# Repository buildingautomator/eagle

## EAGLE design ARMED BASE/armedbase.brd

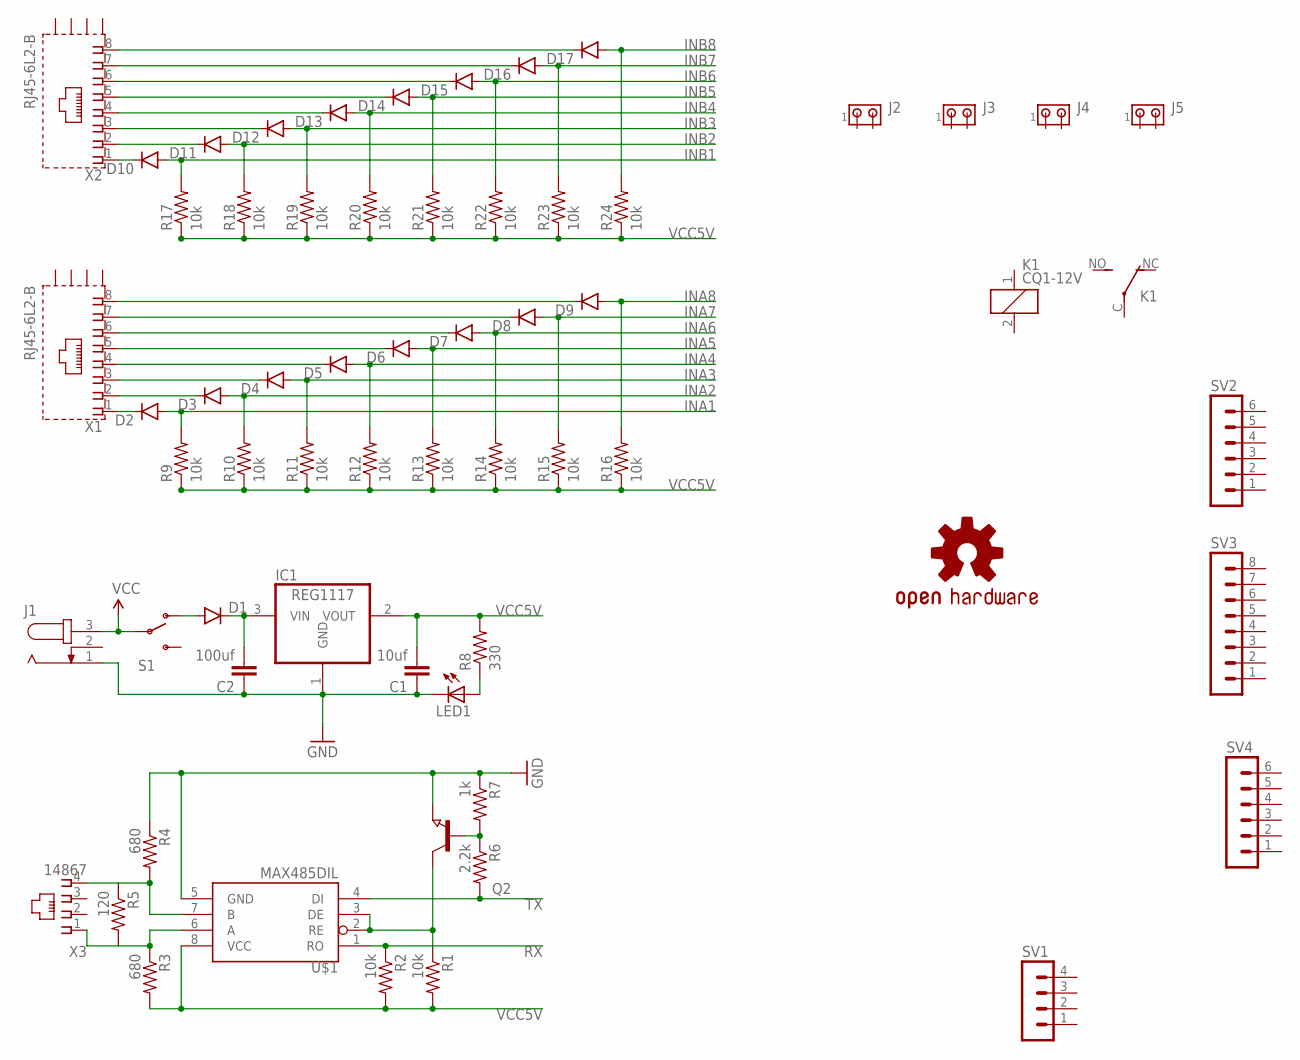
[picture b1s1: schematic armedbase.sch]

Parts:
C1: 10uf; 0805
C2: 100uf; 0805
D1, D2, D3, D4, D5, D6, D7, D8, D9, D10, D11, D12, D13, D14, D15, D16, D17: DIODESMA; SMA-DIODE
IC1: REG1117; SOT223
J1: JACK-PLUG1; SPC4078
J2, J3, J4, J5: MTA02-156; 1X2MTA
K1: CQ1-12V; CQ1
LED1: LEDCHIP-LED0805; CHIP-LED0805
LOGO2: OSHW-LOGOL; OSHW-LOGO-L
Q2: NPN-TRANSISTOR_SOT23; SOT23
R1, R2, R9, R10, R11, R12, R13, R14, R15, R16, R17, R18, R19, R20, R21, R22, R23, R24: 10k; 0805
R3, R4: 680; 0805
R5: 120; 0805
R6: 2.2k; 0805
R7: 1k; 0805
R8: 330; 0805
S1: SWITCH-SPDTSMD2; SWITCH-SPDT-SMD
SV1: MA04-1
SV2, SV4: MA06-1
SV3: MA08-1
U$1: MAX485DIL; DIL08
X1, X2: RJ45-6L2-B; RJ45-SHIELD2
X3: 14867

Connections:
GND: C1.1, C2.1, IC1.1 (GND), J1.1, LED1.C, Q2.2 (E), R4.1, R7.1, U$1.5 (GND)
INA1: D2.A, R9.2
INA2: D3.A, R10.2
INA3: D4.A, R11.2
INA4: D5.A, R12.2
INA5: D6.A, R13.2
INA6: D7.A, R14.2
INA7: D8.A, R15.2
INA8: D9.A, R16.2
INB1: D10.A, R17.2
INB2: D11.A, R18.2
INB3: D12.A, R19.2
INB4: D13.A, R20.2
INB5: D14.A, R21.2
INB6: D15.A, R22.2
INB7: D16.A, R23.2
INB8: D17.A, R24.2
unnamed: D2.C, X1.1
unnamed: Q2.3 (C), R1.1, U$1.2 (RE), U$1.3 (DE)
unnamed: D10.C, X2.1
unnamed: Q2.1 (B), R6.1, R7.2
unnamed: D11.C, X2.2
unnamed: R4.2, R5.1, U$1.7 (B), X3.4
unnamed: R3.1, R5.2, U$1.6 (A), X3.1
unnamed: D12.C, X2.3
unnamed: D13.C, X2.4
unnamed: LED1.A, R8.1
unnamed: D14.C, X2.5
unnamed: D1.A, S1.1 (O)
unnamed: C2.2, D1.C, IC1.3 (VIN)
unnamed: D15.C, X2.6
unnamed: D16.C, X2.7
unnamed: D17.C, X2.8
unnamed: D3.C, X1.2
unnamed: D4.C, X1.3
unnamed: D5.C, X1.4
unnamed: D6.C, X1.5
unnamed: D7.C, X1.6
unnamed: D8.C, X1.7
unnamed: D9.C, X1.8
RX: R2.1, U$1.1 (RO)
TX: R6.2, U$1.4 (DI)
VCC: J1.3, S1.2
VCC5V: C1.2, IC1.2 (VOUT), R1.2, R2.2, R3.2, R8.2, R9.1, R10.1, R11.1, R12.1, R13.1, R14.1, R15.1, R16.1, R17.1, R18.1, R19.1, R20.1, R21.1, R22.1, R23.1, R24.1, U$1.8 (VCC)

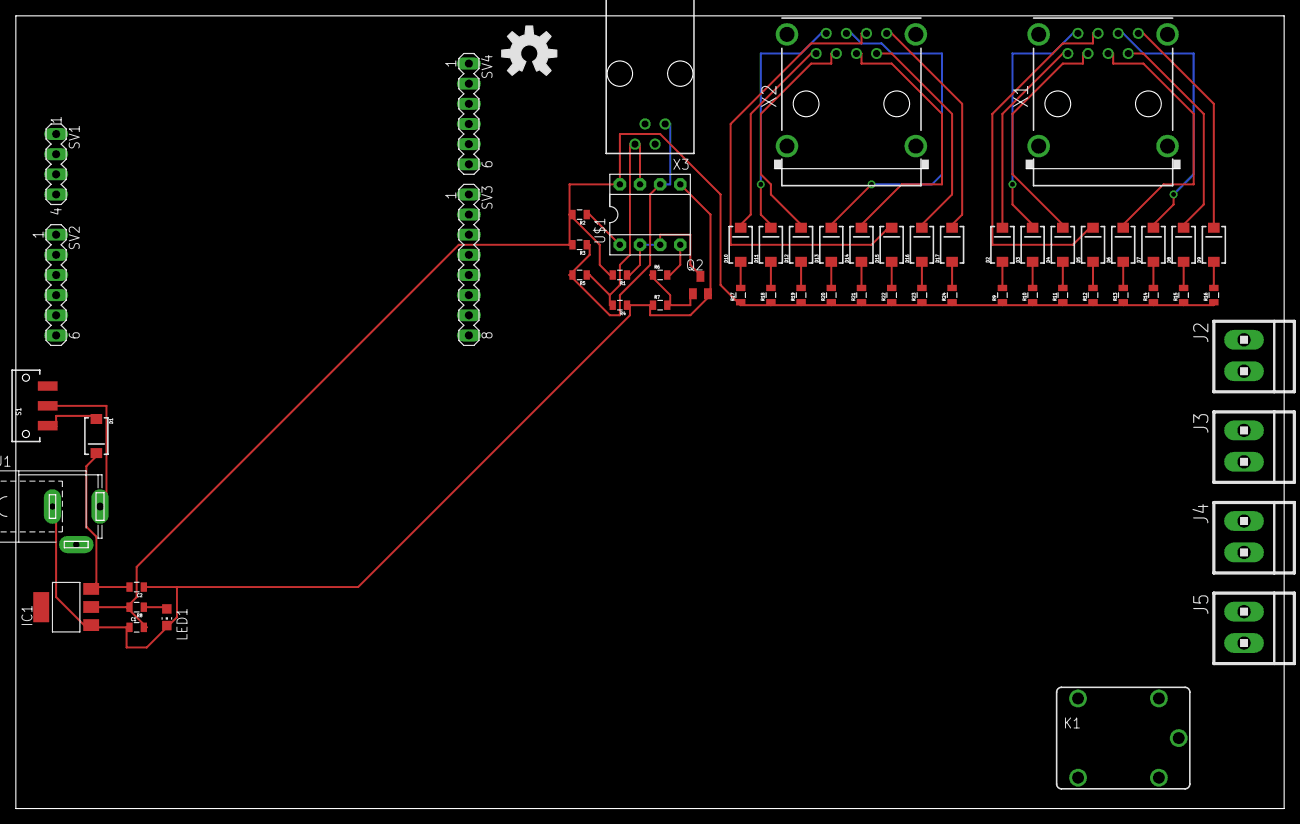
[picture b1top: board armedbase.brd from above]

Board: 2 copper layers, 160.0 x 100.0 mm, 62 parts (0 on the bottom side), 44 nets.

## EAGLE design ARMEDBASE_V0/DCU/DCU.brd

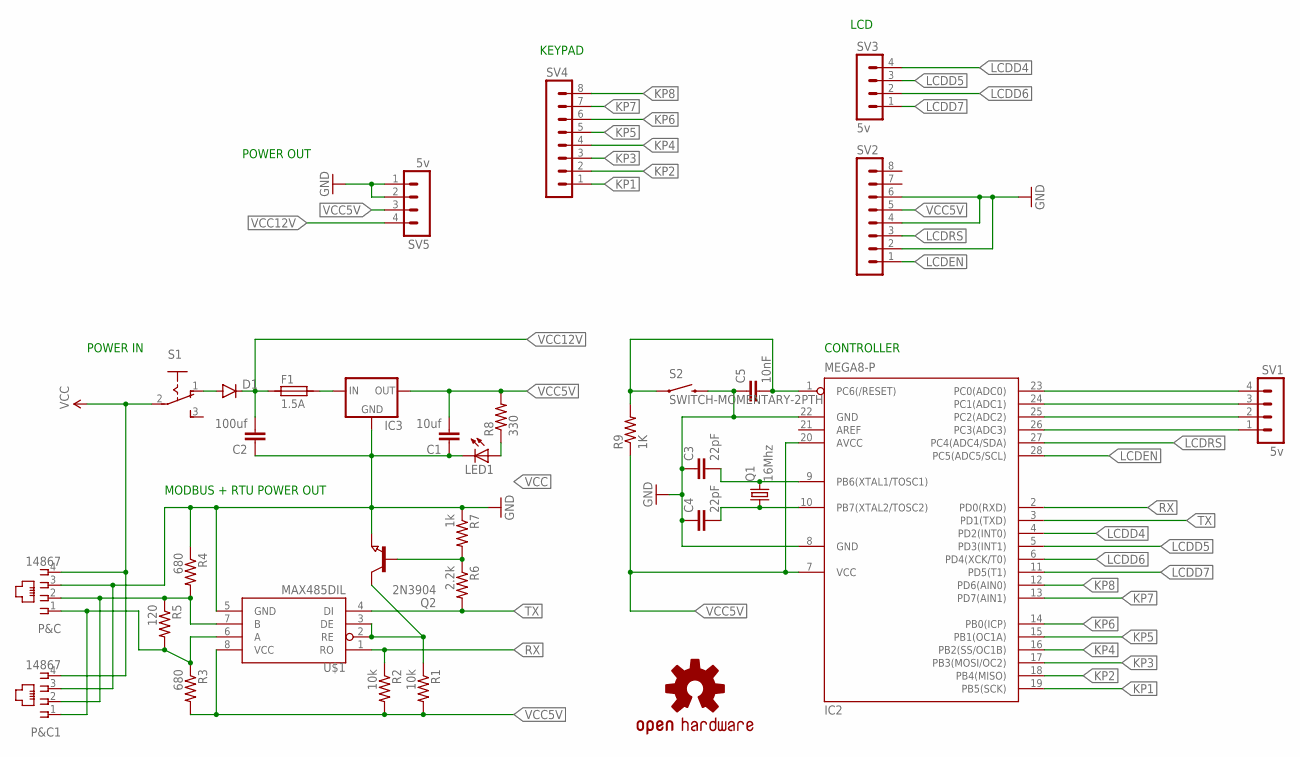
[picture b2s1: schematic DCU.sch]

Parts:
C1: 10uf; 0805
C2: 100uf; 0805
C3, C4: 22pF; 0805
C5: 10nF; 0805
D1: DIODESMA; SMA-DIODE
F1: 1.5A; 1820
IC2: MEGA8-P; DIL28-3
IC3: V_REG_78XX-TO-220; TO-220-ALT
LED1: LEDCHIP-LED0805; CHIP-LED0805
LOGO1: OSHW-LOGOL; OSHW-LOGO-L
P&C, P&C1: 14867
Q1: 16Mhz; SM49
Q2: 2N3904; SOT23
R1, R2: 10k; 0805
R3, R4: 680; 0805
R5: 120; 0805
R6: 2.2k; 0805
R7: 1k; 0805
R8: 330; 0805
R9: 1K; 0805
S1: 255SB
S2: SWITCH-MOMENTARY-2PTH; TACTILE-PTH
SV1, SV3, SV5: 5v; MA04-1
SV2, SV4: MA08-1
U$1: MAX485DIL; DIL08

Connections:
GND: C1.1, C2.1, C3.1, C4.1, C5.1, IC2.8 (GND), IC2.22 (GND), IC3.GND, LED1.C, P&C.3, P&C1.3, Q2.2 (E), R4.1, R7.1, S2.3 (2), SV2.2, SV2.4, SV2.6, SV5.1, SV5.2, U$1.5 (GND)
KP1: IC2.19 (PB5(SCK)), SV4.1
KP2: IC2.18 (PB4(MISO)), SV4.2
KP3: IC2.17 (PB3(MOSI/OC2)), SV4.3
KP4: IC2.16 (PB2(SS/OC1B)), SV4.4
KP5: IC2.15 (PB1(OC1A)), SV4.5
KP6: IC2.14 (PB0(ICP)), SV4.6
KP7: IC2.13 (PD7(AIN1)), SV4.7
KP8: IC2.12 (PD6(AIN0)), SV4.8
LCDD4: IC2.4 (PD2(INT0)), SV3.4
LCDD5: IC2.5 (PD3(INT1)), SV3.3
LCDD6: IC2.6 (PD4(XCK/T0)), SV3.2
LCDD7: IC2.11 (PD5(T1)), SV3.1
LCDEN: IC2.28 (PC5(ADC5/SCL)), SV2.1
LCDRS: IC2.27 (PC4(ADC4/SDA)), SV2.3
unnamed: F1.2, IC3.IN
unnamed: Q2.3 (C), R1.1, U$1.2 (RE), U$1.3 (DE)
unnamed: Q2.1 (B), R6.1, R7.2
unnamed: IC2.26 (PC3(ADC3)), SV1.1
unnamed: P&C.2, P&C1.2, R4.2, R5.1, U$1.7 (B)
unnamed: P&C.1, P&C1.1, R3.1, R5.2, U$1.6 (A)
unnamed: LED1.A, R8.1
unnamed: D1.A, S1.1 (O)
unnamed: IC2.25 (PC2(ADC2)), SV1.2
unnamed: IC2.24 (PC1(ADC1)), SV1.3
unnamed: IC2.23 (PC0(ADC0)), SV1.4
unnamed: C3.2, IC2.9 (PB6(XTAL1/TOSC1)), Q1.2
unnamed: C4.2, IC2.10 (PB7(XTAL2/TOSC2)), Q1.1
unnamed: C5.2, IC2.1 (PC6(/RESET)), R9.2, S2.1
RX: IC2.2 (PD0(RXD)), R2.1, U$1.1 (RO)
TX: IC2.3 (PD1(TXD)), R6.2, U$1.4 (DI)
VCC: P&C.4, P&C1.4, S1.2
VCC5V: C1.2, IC2.7 (VCC), IC2.20 (AVCC), IC3.OUT, R1.2, R2.2, R3.2, R8.2, R9.1, SV2.5, SV5.3, U$1.8 (VCC)
VCC12V: C2.2, D1.C, F1.1, SV5.4

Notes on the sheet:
LCD
KEYPAD
POWER OUT
POWER IN
MODBUS + RTU POWER OUT
CONTROLLER

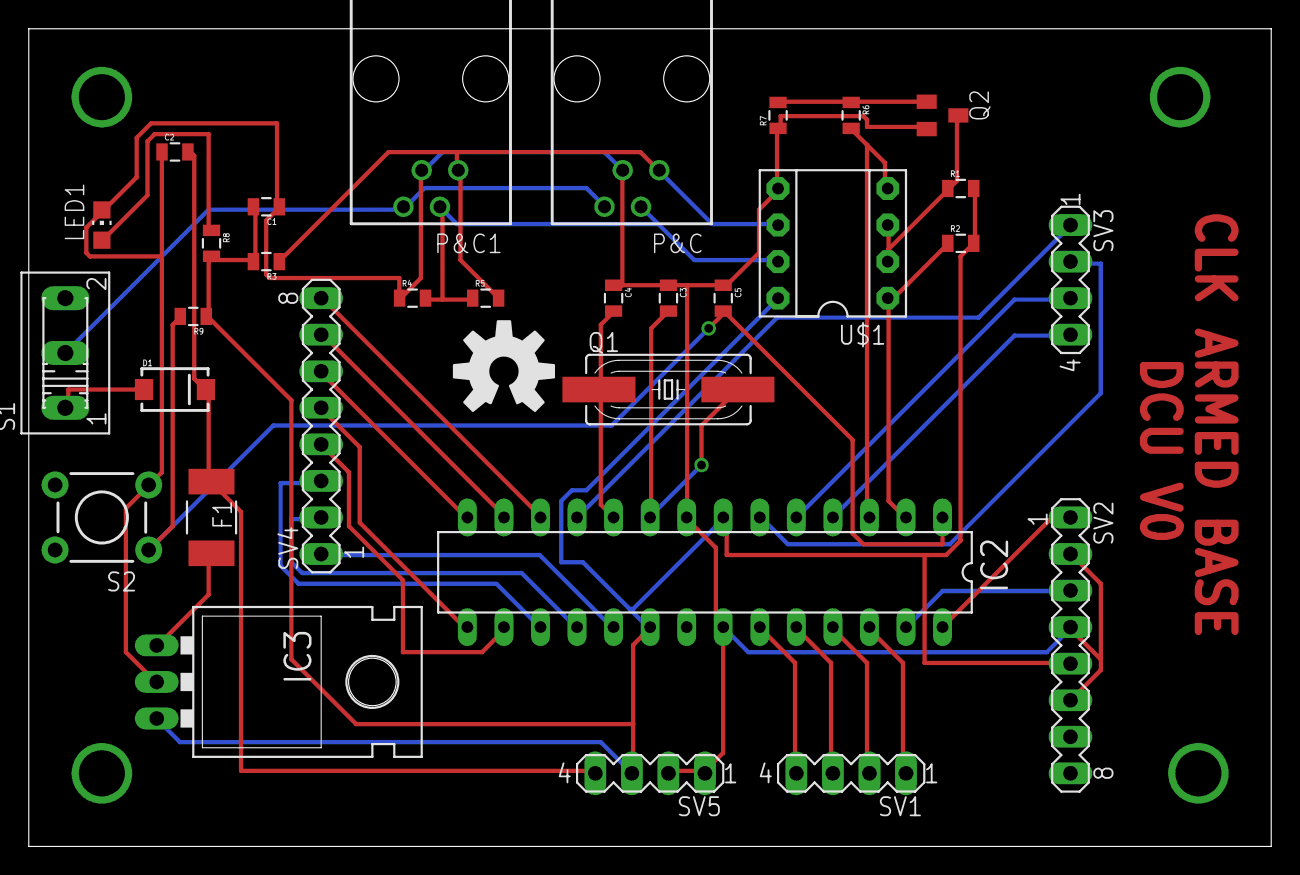
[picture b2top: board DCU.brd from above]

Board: 2 copper layers, 86.3 x 56.8 mm, 32 parts (0 on the bottom side), 34 nets.

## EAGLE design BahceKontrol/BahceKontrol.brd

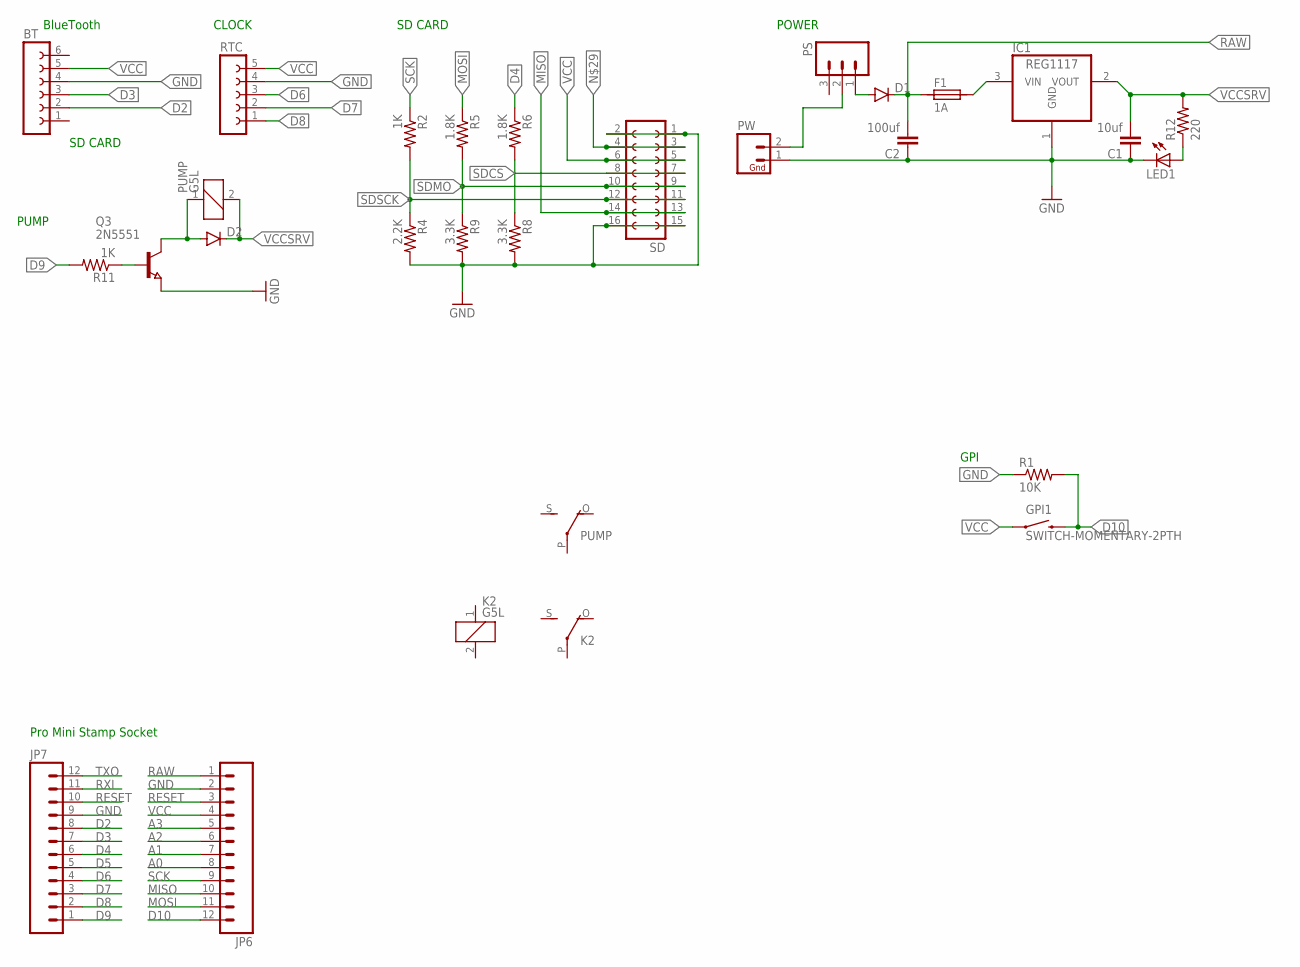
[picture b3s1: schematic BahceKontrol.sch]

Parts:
BT: FE06-1; FE06
C1: 10uf; 0805
C2: 100uf; 0805
D1, D2: DIODESMA; SMA-DIODE
F1: 1A; 1820
GPI1: SWITCH-MOMENTARY-2PTH; TACTILE-PTH
IC1: REG1117; SOT223
JP6, JP7: M12PTH; 1X12
K2: G5L; G5LE
LED1: LEDCHIP-LED0805; CHIP-LED0805
PS: M03PTH; 1X03
PUMP: G5L; G5LE
PW: M02PTH; 1X02
Q3: 2N5551; SOT23
R1: 10K; 0805
R2, R11: 1K; 0805
R4: 2.2K; 0805
R5, R6: 1.8K; 0805
R8, R9: 3.3K; 0805
R12: 220; 0805
RTC: FE05-1
SD: FE08-2

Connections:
A0: JP6.8
A1: JP6.7
A2: JP6.6
A3: JP6.5
D2: BT.2, JP7.8
D3: BT.3, JP7.7
D4: JP7.6, R6.1
D5: JP7.5
D6: JP7.4, RTC.3
D7: JP7.3, RTC.2
D8: JP7.2, RTC.1
D9: JP7.1, R11.2
D10: GPI1.3 (2), JP6.12, R1.2
GND: BT.4, C1.1, C2.1, IC1.1 (GND), JP6.2, JP7.9, LED1.C, PW.1, Q3.2 (E), R1.1, R4.2, R8.2, R9.2, RTC.4, SD.1, SD.2, SD.15, SD.16
MISO: JP6.10, SD.13, SD.14
MOSI: JP6.11, R5.1
unnamed: F1.2, IC1.3 (VIN)
unnamed: PS.2, PW.2
unnamed: D2.A, PUMP.1, Q3.3 (C)
unnamed: Q3.1 (B), R11.1
unnamed: LED1.A, R12.1
unnamed: D1.A, PS.1
unnamed: SD.3, SD.4
RAW: C2.2, D1.C, F1.1, JP6.1
RESET: JP6.3, JP7.10
RXI: JP7.11
SCK: JP6.9, R2.1
SDCS: R6.2, R8.1, SD.7, SD.8
SDMO: R5.2, R9.1, SD.9, SD.10
SDSCK: R2.2, R4.1, SD.11, SD.12
TXO: JP7.12
VCC: BT.5, GPI1.1, JP6.4, RTC.5, SD.5, SD.6
VCCSRV: C1.2, D2.C, IC1.2 (VOUT), PUMP.2, R12.2

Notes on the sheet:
PUMP
Pro Mini Stamp Socket
POWER
CLOCK
BlueTooth
SD CARD
GPI

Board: 2 copper layers, 27 parts (3 on the bottom side), 26 nets, no tracks yet.

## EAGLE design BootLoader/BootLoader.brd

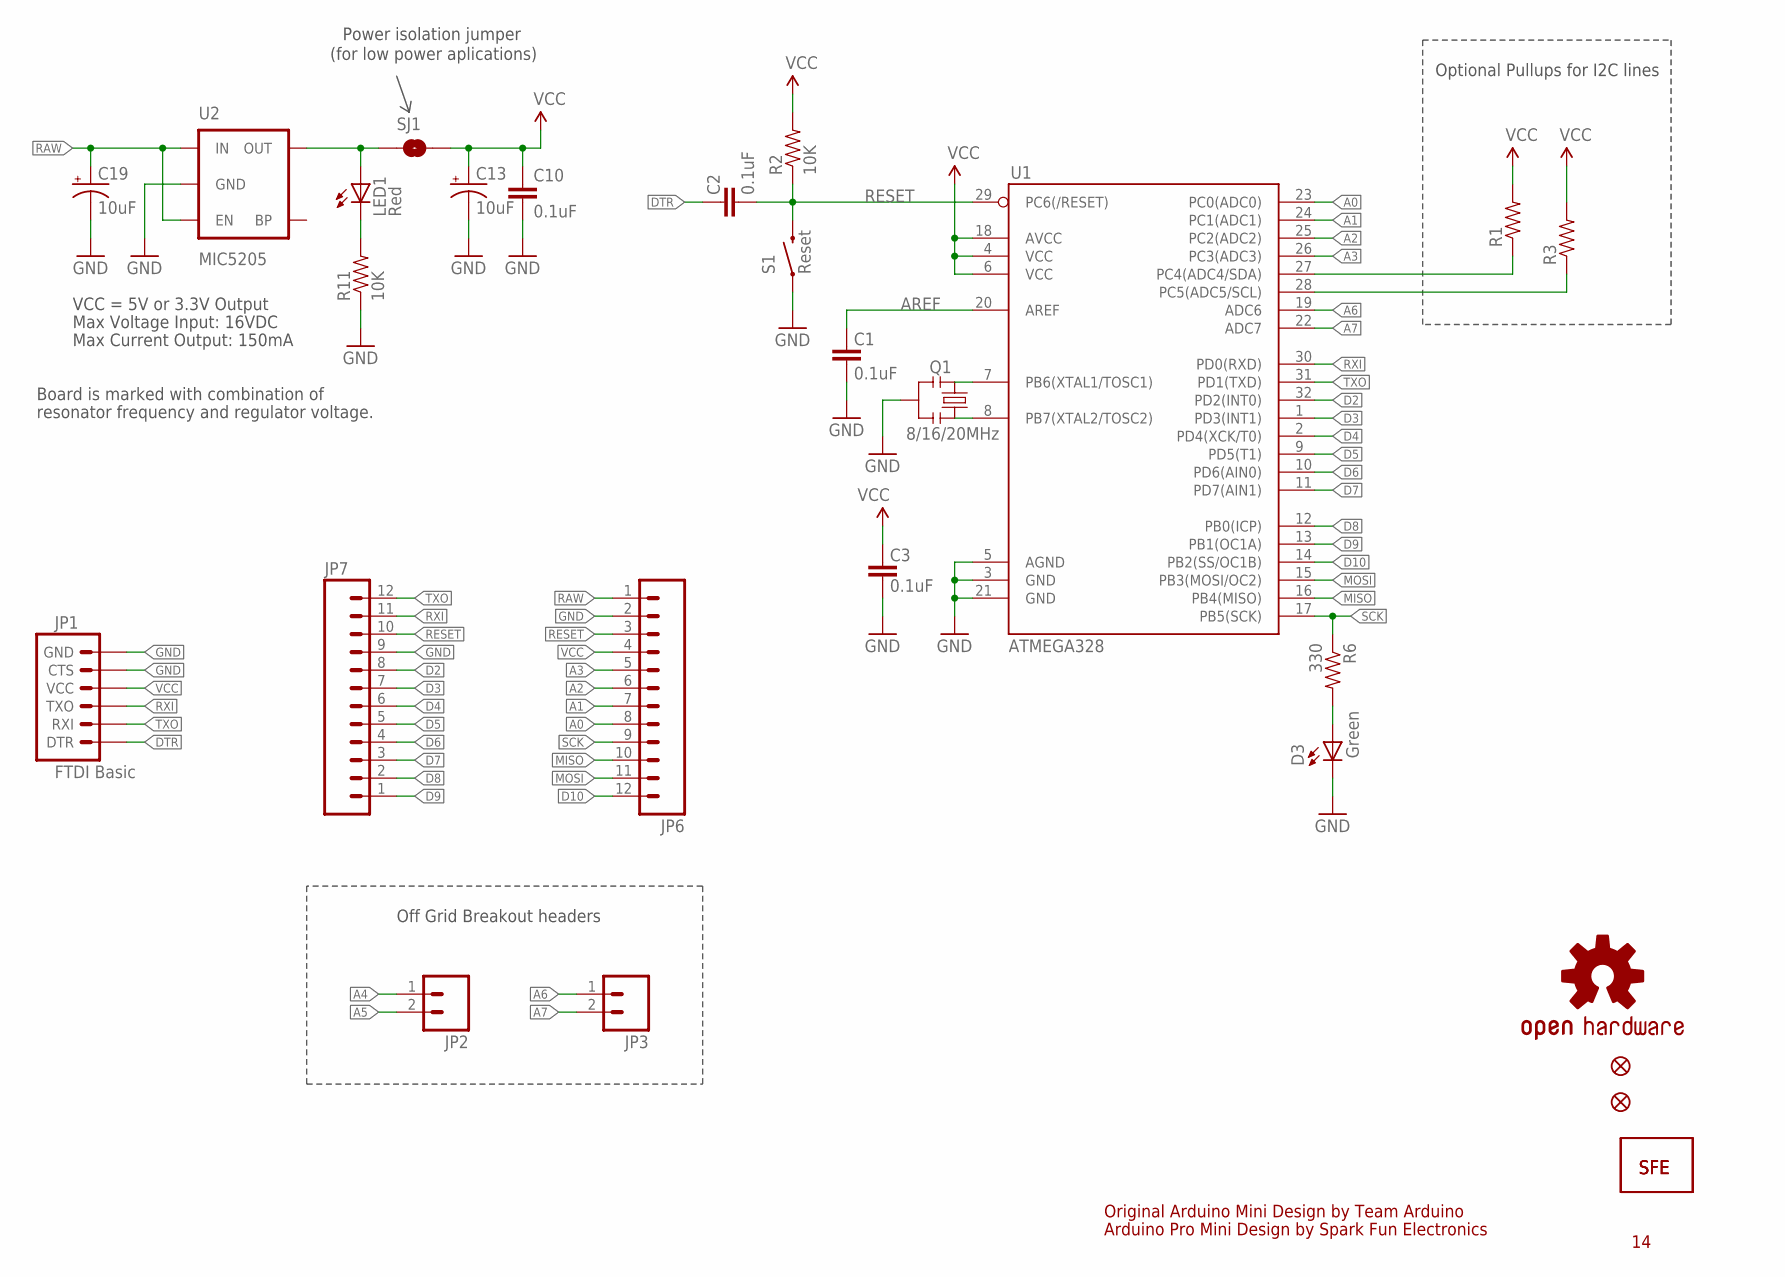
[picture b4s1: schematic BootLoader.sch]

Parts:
C1, C2, C3, C10: 0.1uF; 0603-CAP
C13, C19: 10uF; EIA3216
D3: Green; 0603-LED-ALT1
JP1: FTDI Basic; 1X06
JP2, JP3: M02PTH; 1X02
JP5, JP8: FIDUCIALUFIDUCIAL; MICRO-FIDUCIAL
JP6, JP7: M12PTH; 1X12
LED1: Red; 0603-LED-ALT1
Q1: 8/16/20MHz; RESONATOR-SMD-1:1
R1, R3: RESISTOR0603-RES; 0603-RES
R2, R11: 10K; 0603-RES
R6: 330; 0603-RES
S1: Reset; TACTILE-SWITCH-SMD-ALT01
SJ1: SOLDERJUMPERNC; SJ_2S
U1: ATMEGA328; TQFP32-08
U2: MIC5205; SOT23-5
U$1: LOGO-SFESK; SFE-LOGO-FLAME
U$3: OSHW-LOGOS; OSHW-LOGO-S
U$11: LOGO-SFENEW; SFE-NEW-WEBLOGO

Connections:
A0: JP6.8, U1.23 (PC0(ADC0))
A1: JP6.7, U1.24 (PC1(ADC1))
A2: JP6.6, U1.25 (PC2(ADC2))
A3: JP6.5, U1.26 (PC3(ADC3))
A4: JP2.1, R1.1, U1.27 (PC4(ADC4/SDA))
A5: JP2.2, R3.1, U1.28 (PC5(ADC5/SCL))
A6: JP3.1, U1.19 (ADC6)
A7: JP3.2, U1.22 (ADC7)
AREF: C1.2, U1.20 (AREF)
D2: JP7.8, U1.32 (PD2(INT0))
D3: JP7.7, U1.1 (PD3(INT1))
D4: JP7.6, U1.2 (PD4(XCK/T0))
D5: JP7.5, U1.9 (PD5(T1))
D6: JP7.4, U1.10 (PD6(AIN0))
D7: JP7.3, U1.11 (PD7(AIN1))
D8: JP7.2, U1.12 (PB0(ICP))
D9: JP7.1, U1.13 (PB1(OC1A))
D10: JP6.12, U1.14 (PB2(SS/OC1B))
DTR: C2.2, JP1.1 (DTR)
GND: C1.1, C3.1, C10.2, C13.C (-), C19.C (-), D3.C, JP1.5 (CTS), JP1.6 (GND), JP6.2, JP7.9, Q1.2, R11.1, S1.1, S1.2 (1), U1.3 (GND), U1.5 (AGND), U1.21 (GND), U2.2 (GND)
MISO: JP6.10, U1.16 (PB4(MISO))
MOSI: JP6.11, U1.15 (PB3(MOSI/OC2))
unnamed: Q1.3, U1.8 (PB7(XTAL2/TOSC2))
unnamed: Q1.1, U1.7 (PB6(XTAL1/TOSC1))
unnamed: LED1.A, SJ1.1, U2.5 (OUT)
unnamed: LED1.C, R11.2
unnamed: D3.A, R6.2
RAW: C19.A (+), JP6.1, U2.1 (IN), U2.3 (EN)
RESET: C2.1, JP6.3, JP7.10, R2.1, S1.3 (2), S1.4 (2), U1.29 (PC6(/RESET))
RXI: JP1.3 (TXO), JP7.11, U1.30 (PD0(RXD))
SCK: JP6.9, R6.1, U1.17 (PB5(SCK))
TXO: JP1.2 (RXI), JP7.12, U1.31 (PD1(TXD))
VCC: C3.2, C10.1, C13.A (+), JP1.4 (VCC), JP6.4, R1.2, R2.2, R3.2, SJ1.2, U1.4 (VCC), U1.6 (VCC), U1.18 (AVCC)

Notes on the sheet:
Original Arduino Mini Design by Team Arduino
Arduino Pro Mini Design by Spark Fun Electronics
Max Voltage Input: 16VDC
Max Current Output: 150mA
Board is marked with combination of
resonator frequency and regulator voltage.
VCC = 5V or 3.3V Output
Optional Pullups for I2C lines
Off Grid Breakout headers
Power isolation jumper
(for low power aplications)

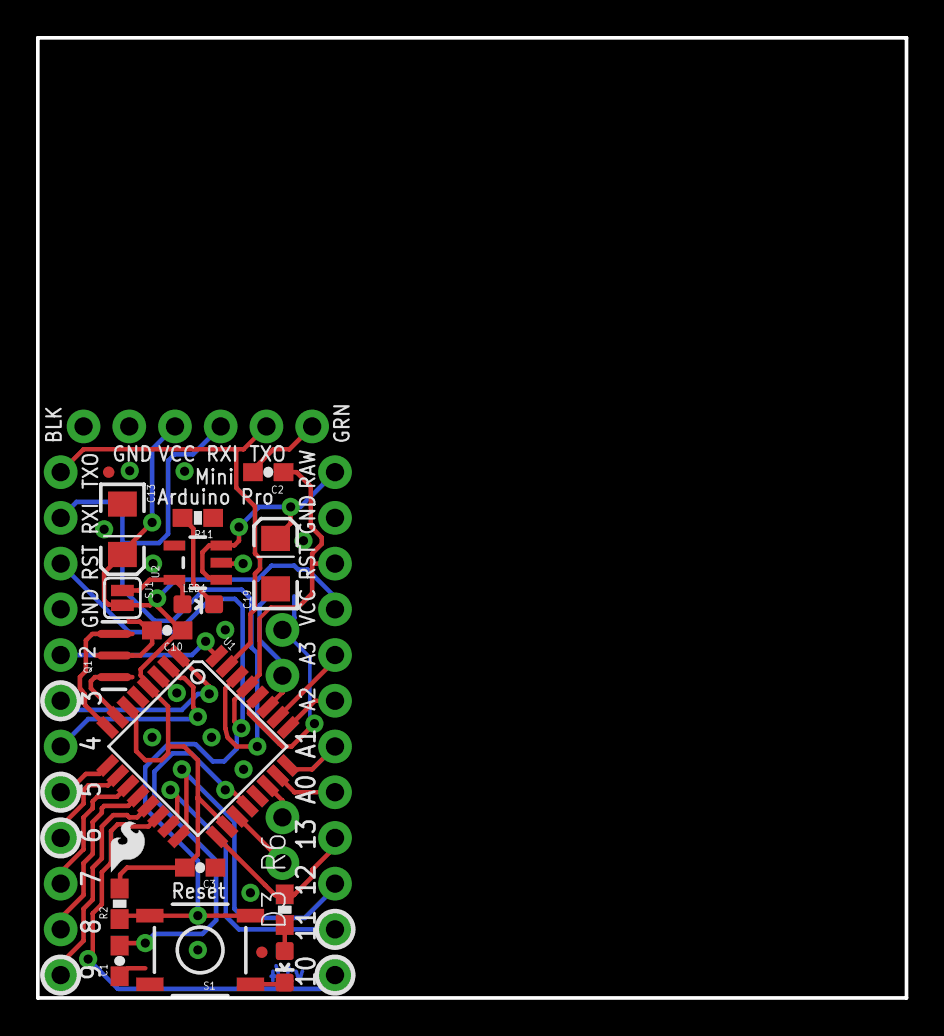
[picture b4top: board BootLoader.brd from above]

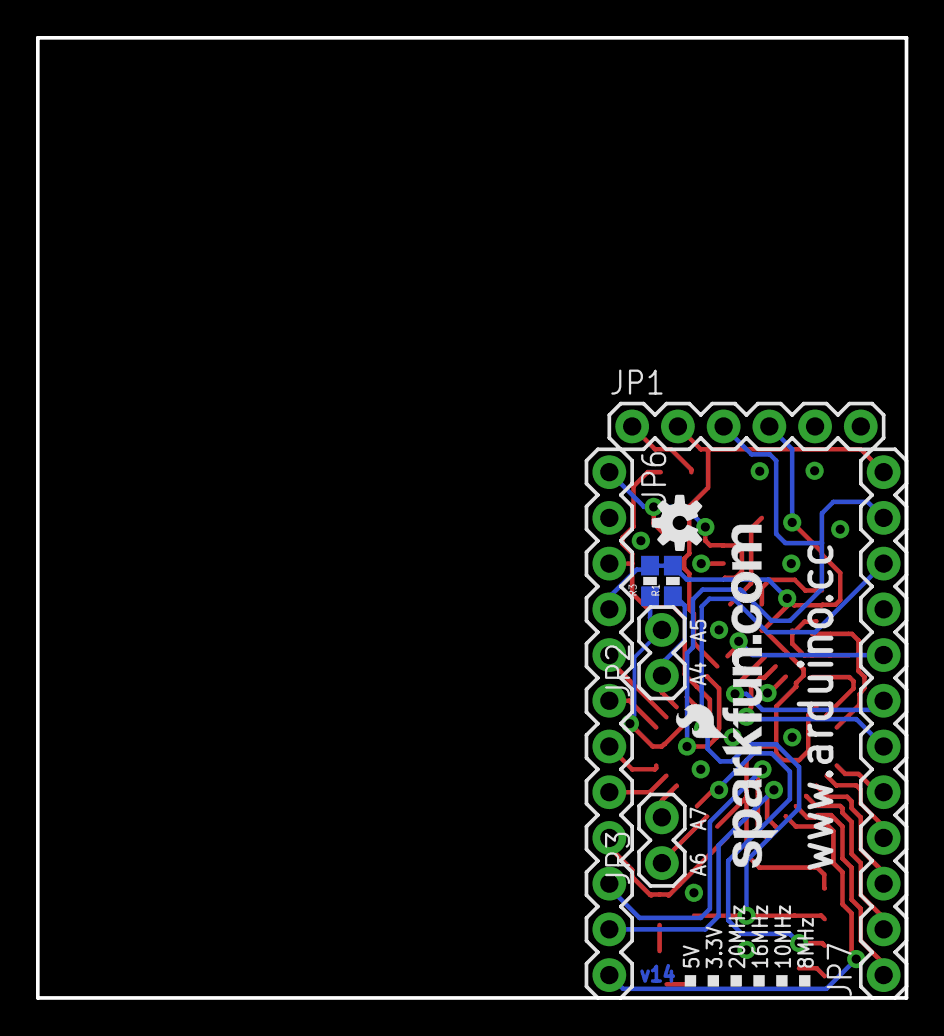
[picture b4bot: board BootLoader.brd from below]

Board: 2 copper layers, 48.3 x 53.3 mm, 28 parts (9 on the bottom side), 33 nets.

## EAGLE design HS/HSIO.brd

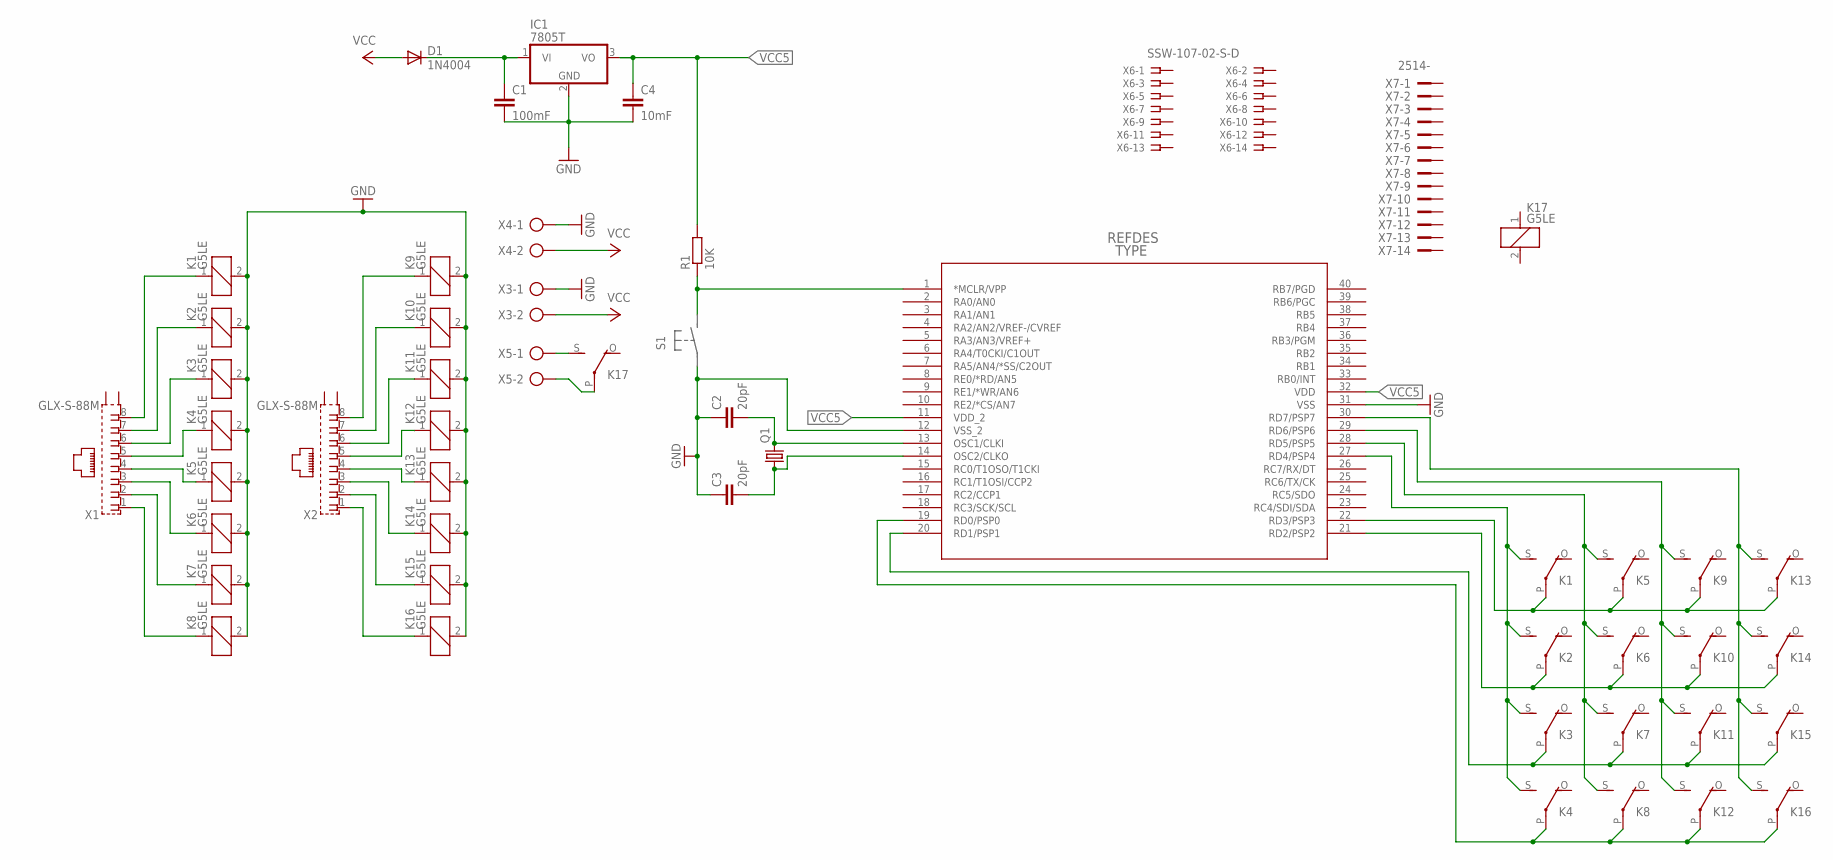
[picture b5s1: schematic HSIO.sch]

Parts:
C1: 100mF; C10B4
C2, C3: 20pF; C10B4
C4: 10mF; C10B4
D1: 1N4004; DO41-10
IC1: 7805T; TO220H
K1, K2, K3, K4, K5, K6, K7, K8, K9, K10, K11, K12, K13, K14, K15, K16, K17: G5LE
Q1: CRYSTALHC49S; HC49/S
R1: 10K; 0207/10
U$1: PIC16F877A-X/P; PDIP40_600MC
X1, X2: GLX-S-88M
X3, X4, X5: AK300/2
X6: SSW-107-02-S-D
X7: 2514-; PAK100/2500-14

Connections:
GND: C1.2, C2.1, C3.1, C4.2, IC1.2 (GND), K1.2, K2.2, K3.2, K4.2, K5.2, K6.2, K7.2, K8.2, K9.2, K10.2, K11.2, K12.2, K13.2, K14.2, K15.2, K16.2, U$1.12 (VSS_2), U$1.31 (VSS), X3.1, X4.1
unnamed: K1.1, X1.8
unnamed: K2.1, X1.7
unnamed: K3.1, X1.6
unnamed: K4.1, X1.5
unnamed: K5.1, X1.4
unnamed: K9.1, X2.8
unnamed: K10.1, X2.7
unnamed: K11.1, X2.6
unnamed: K6.1, X1.3
unnamed: K7.1, X1.2
unnamed: K8.1, X1.1
unnamed: K12.1, X2.5
unnamed: K13.1, X2.4
unnamed: K14.1, X2.3
unnamed: K17.S, X5.1
unnamed: K17.P, X5.2
unnamed: K15.1, X2.2
unnamed: K16.1, X2.1
unnamed: K1.S, K2.S, K3.S, K4.S, U$1.27 (RD4/PSP4)
unnamed: K5.S, K6.S, K7.S, K8.S, U$1.28 (RD5/PSP5)
unnamed: K9.S, K10.S, K11.S, K12.S, U$1.29 (RD6/PSP6)
unnamed: K13.S, K14.S, K15.S, K16.S, U$1.30 (RD7/PSP7)
unnamed: K1.P, K5.P, K9.P, K13.P, U$1.22 (RD3/PSP3)
unnamed: K2.P, K6.P, K10.P, K14.P, U$1.21 (RD2/PSP2)
unnamed: K3.P, K7.P, K11.P, K15.P, U$1.20 (RD1/PSP1)
unnamed: K4.P, K8.P, K12.P, K16.P, U$1.19 (RD0/PSP0)
unnamed: C2.2, Q1.2, U$1.13 (OSC1/CLKI)
unnamed: R1.1, U$1.1 (*MCLR/VPP)
unnamed: C1.1, D1.C, IC1.1 (VI)
unnamed: C3.2, Q1.1, U$1.14 (OSC2/CLKO)
VCC: D1.A, X3.2, X4.2
VCC5: C4.1, IC1.3 (VO), R1.2, U$1.11 (VDD_2), U$1.32 (VDD)

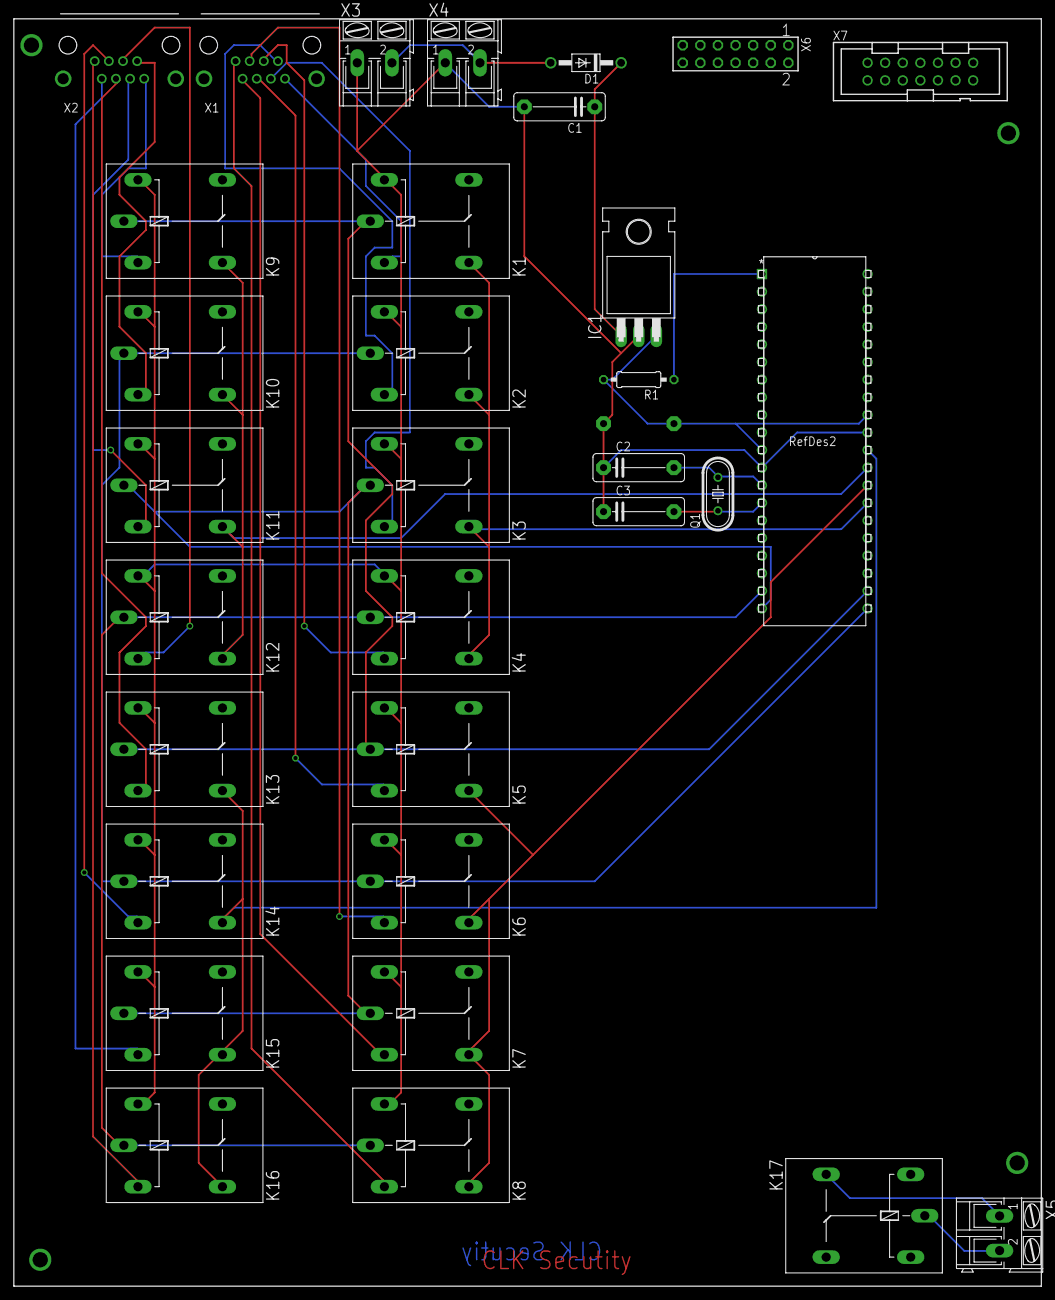
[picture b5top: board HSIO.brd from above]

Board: 2 copper layers, 148.3 x 183.6 mm, 33 parts (1 on the bottom side), 33 nets.

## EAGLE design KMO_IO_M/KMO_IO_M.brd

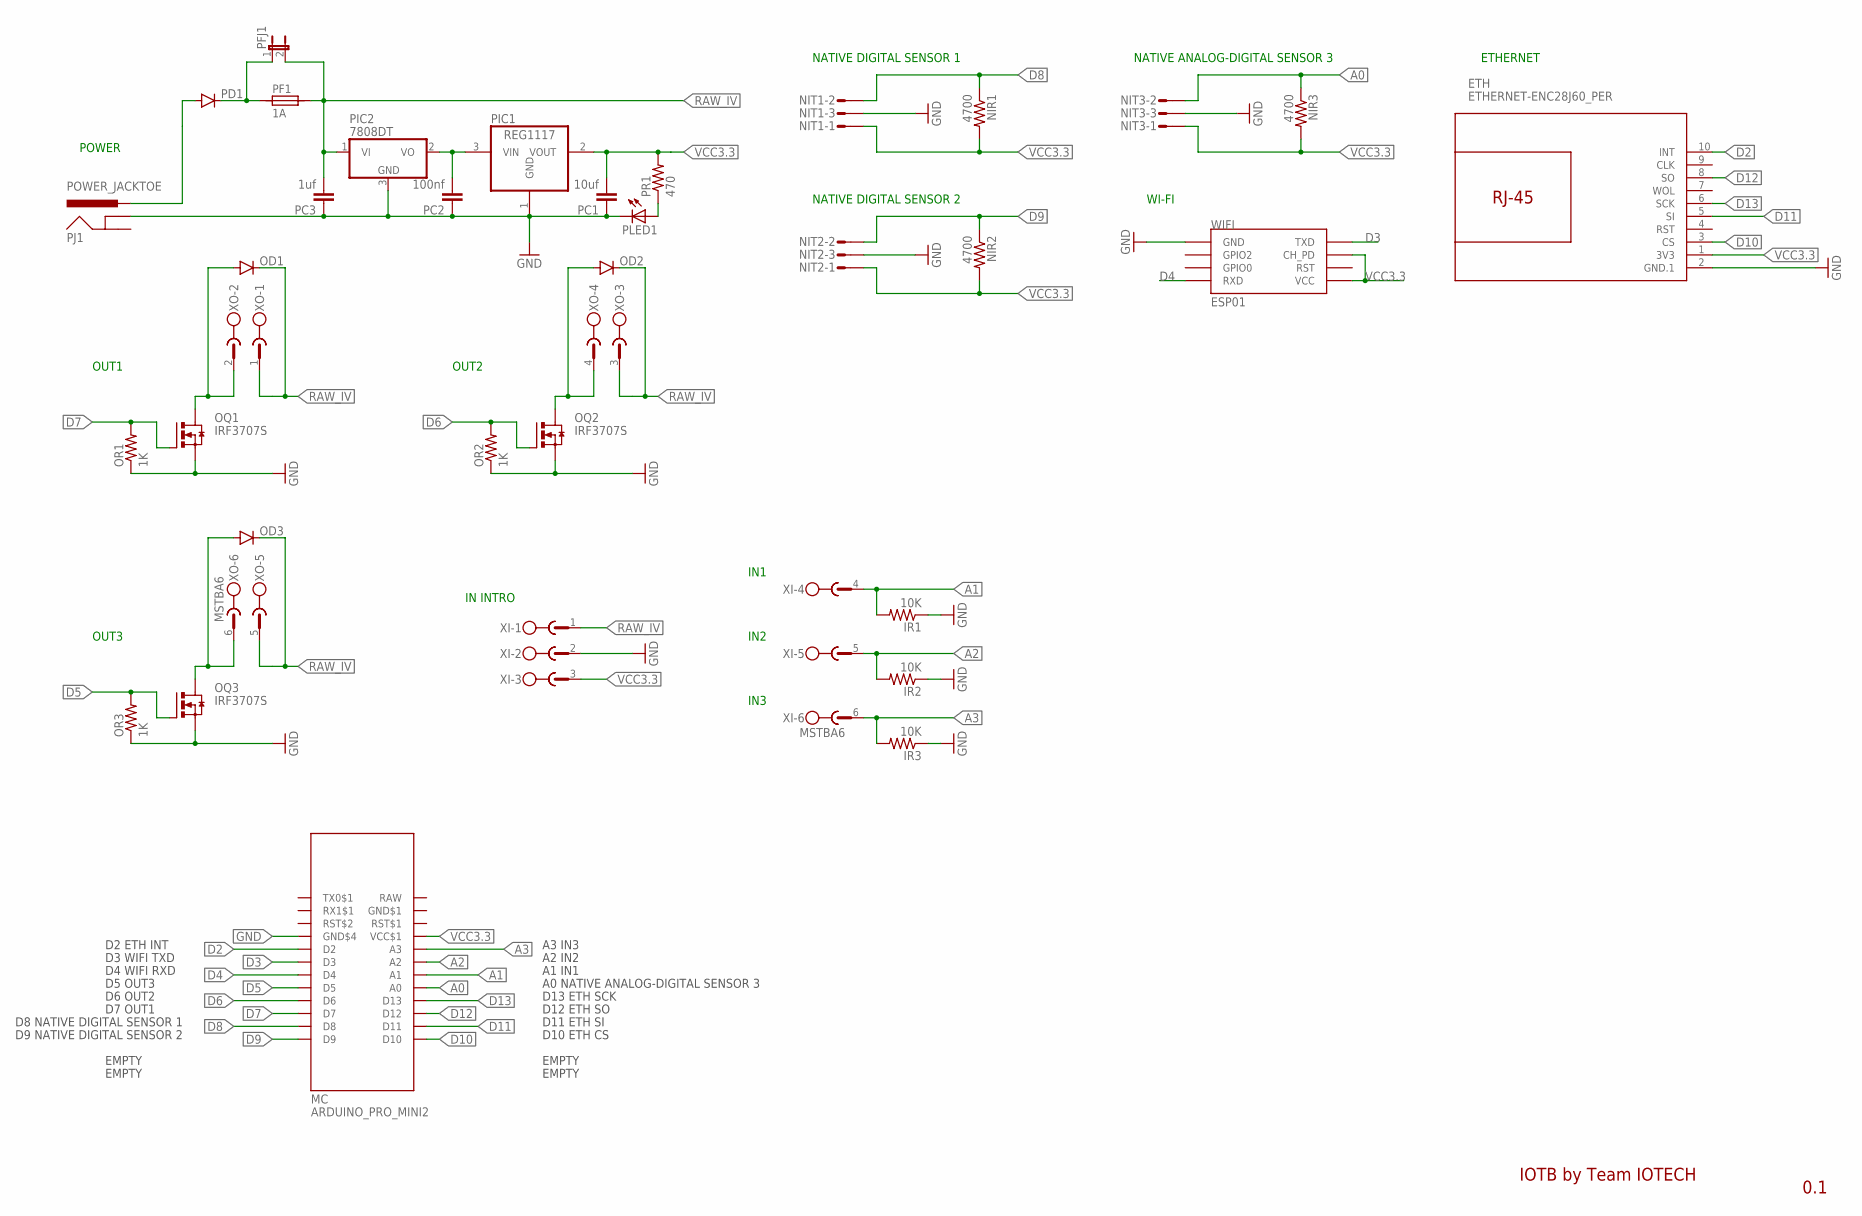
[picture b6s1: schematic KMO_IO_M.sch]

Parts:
ETH: ETHERNET-ENC28J60_PER
IR1, IR2, IR3: 10K; 0805
MC: ARDUINO_PRO_MINI2
NIR1, NIR2, NIR3: 4700; 0805
NIT1, NIT2, NIT3: S03P
OD1, OD2, OD3: DIODESMA; SMA-DIODE
OQ1, OQ2, OQ3: IRF3707S; D2PACK
OR1, OR2, OR3: 1K; 0805
PC1: 10uf; 0805
PC2: 100nf; 0805
PC3: 1uf; 0805
PD1: DIODESMA; SMA-DIODE
PF1: 1A; 1820
PFJ1: JP1E; JP1
PIC1: REG1117; SOT223
PIC2: 7808DT; TO252
PJ1: POWER_JACKTOE; POWER_JACK_SMD_OVERPASTE_TOE
PLED1: LEDCHIP-LED0805; CHIP-LED0805
PR1: 470; 0805
WIFI: ESP01
XI: MSTBA6
XO: MSTBA6

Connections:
A0: MC.A0, NIR3.1, NIT3.2
A1: IR1.2, MC.A1, XI.4
A2: IR2.2, MC.A2, XI.5
A3: IR3.2, MC.A3, XI.6
D2: ETH.10 (INT), MC.D2
D3: MC.D3, WIFI.TX (TXD)
D4: MC.D4, WIFI.RX (RXD)
D5: MC.D5, OQ3.1 (G), OR3.2
D6: MC.D6, OQ2.1 (G), OR2.2
D7: MC.D7, OQ1.1 (G), OR1.2
D8: MC.D8, NIR1.1, NIT1.2
D9: MC.D9, NIR2.1, NIT2.2
D10: ETH.3 (CS), MC.D10
D11: ETH.5 (SI), MC.D11
D12: ETH.8 (SO), MC.D12
D13: ETH.6 (SCK), MC.D13
GND: ETH.2 (GND.1), IR1.1, IR2.1, IR3.1, MC.GND$4, NIT1.3, NIT2.3, NIT3.3, OQ1.3 (S), OQ2.3 (S), OQ3.3 (S), OR1.1, OR2.1, OR3.1, PC1.1, PC2.1, PC3.1, PIC1.1 (GND), PIC2.3 (GND), PJ1.GND (GNDBREAK), PLED1.C, WIFI.GND, XI.2
GND$1: MC.GDN$1 (GND$1)
unnamed: OD3.A, OQ3.2 (D), XO.6
unnamed: PD1.C, PF1.1, PFJ1.1
unnamed: OD1.A, OQ1.2 (D), XO.2
unnamed: OD2.A, OQ2.2 (D), XO.4
unnamed: PD1.A, PJ1.VIN0 (PWR)
unnamed: PLED1.A, PR1.1
unnamed: PC2.2, PIC1.3 (VIN), PIC2.2 (VO)
RAW: MC.RAW
RAW_IV: OD1.C, OD2.C, OD3.C, PC3.2, PF1.2, PFJ1.2, PIC2.1 (VI), XI.1, XO.1, XO.3, XO.5
VCC3.3: ETH.1 (3V3), MC.VCC$1, NIR1.2, NIR2.2, NIR3.2, NIT1.1, NIT2.1, NIT3.1, PC1.2, PIC1.2 (VOUT), PR1.2, WIFI.CH_PD, WIFI.VCC, XI.3

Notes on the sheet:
POWER
OUT1
NATIVE DIGITAL SENSOR 1
IN INTRO
NATIVE DIGITAL SENSOR 2
OUT2
WI-FI
ETHERNET
D2 ETH INT
D8 NATIVE DIGITAL SENSOR 1
D9 NATIVE DIGITAL SENSOR 2
EMPTY
A3 IN3
A2 IN2
A1 IN1
A0 NATIVE ANALOG-DIGITAL SENSOR 3
D13 ETH SCK
D12 ETH SO
D11 ETH SI
D10 ETH CS
OUT3
D4 WIFI RXD
D3 WIFI TXD
D7 OUT1
D6 OUT2
D5 OUT3
NATIVE ANALOG-DIGITAL SENSOR 3
IN1
IN2
IN3
IOTB by Team IOTECH
0.1

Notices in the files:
parts and their libraries:
SparkFun-DiscreteSemi: Licensing: Creative Commons ShareAlike 4.0 International - https://creativecommons.org/licenses/by-sa/4.0
SparkFun-Passives: Licensing: CC v3.0 Share-Alike You are welcome to use this library for commercial purposes.
